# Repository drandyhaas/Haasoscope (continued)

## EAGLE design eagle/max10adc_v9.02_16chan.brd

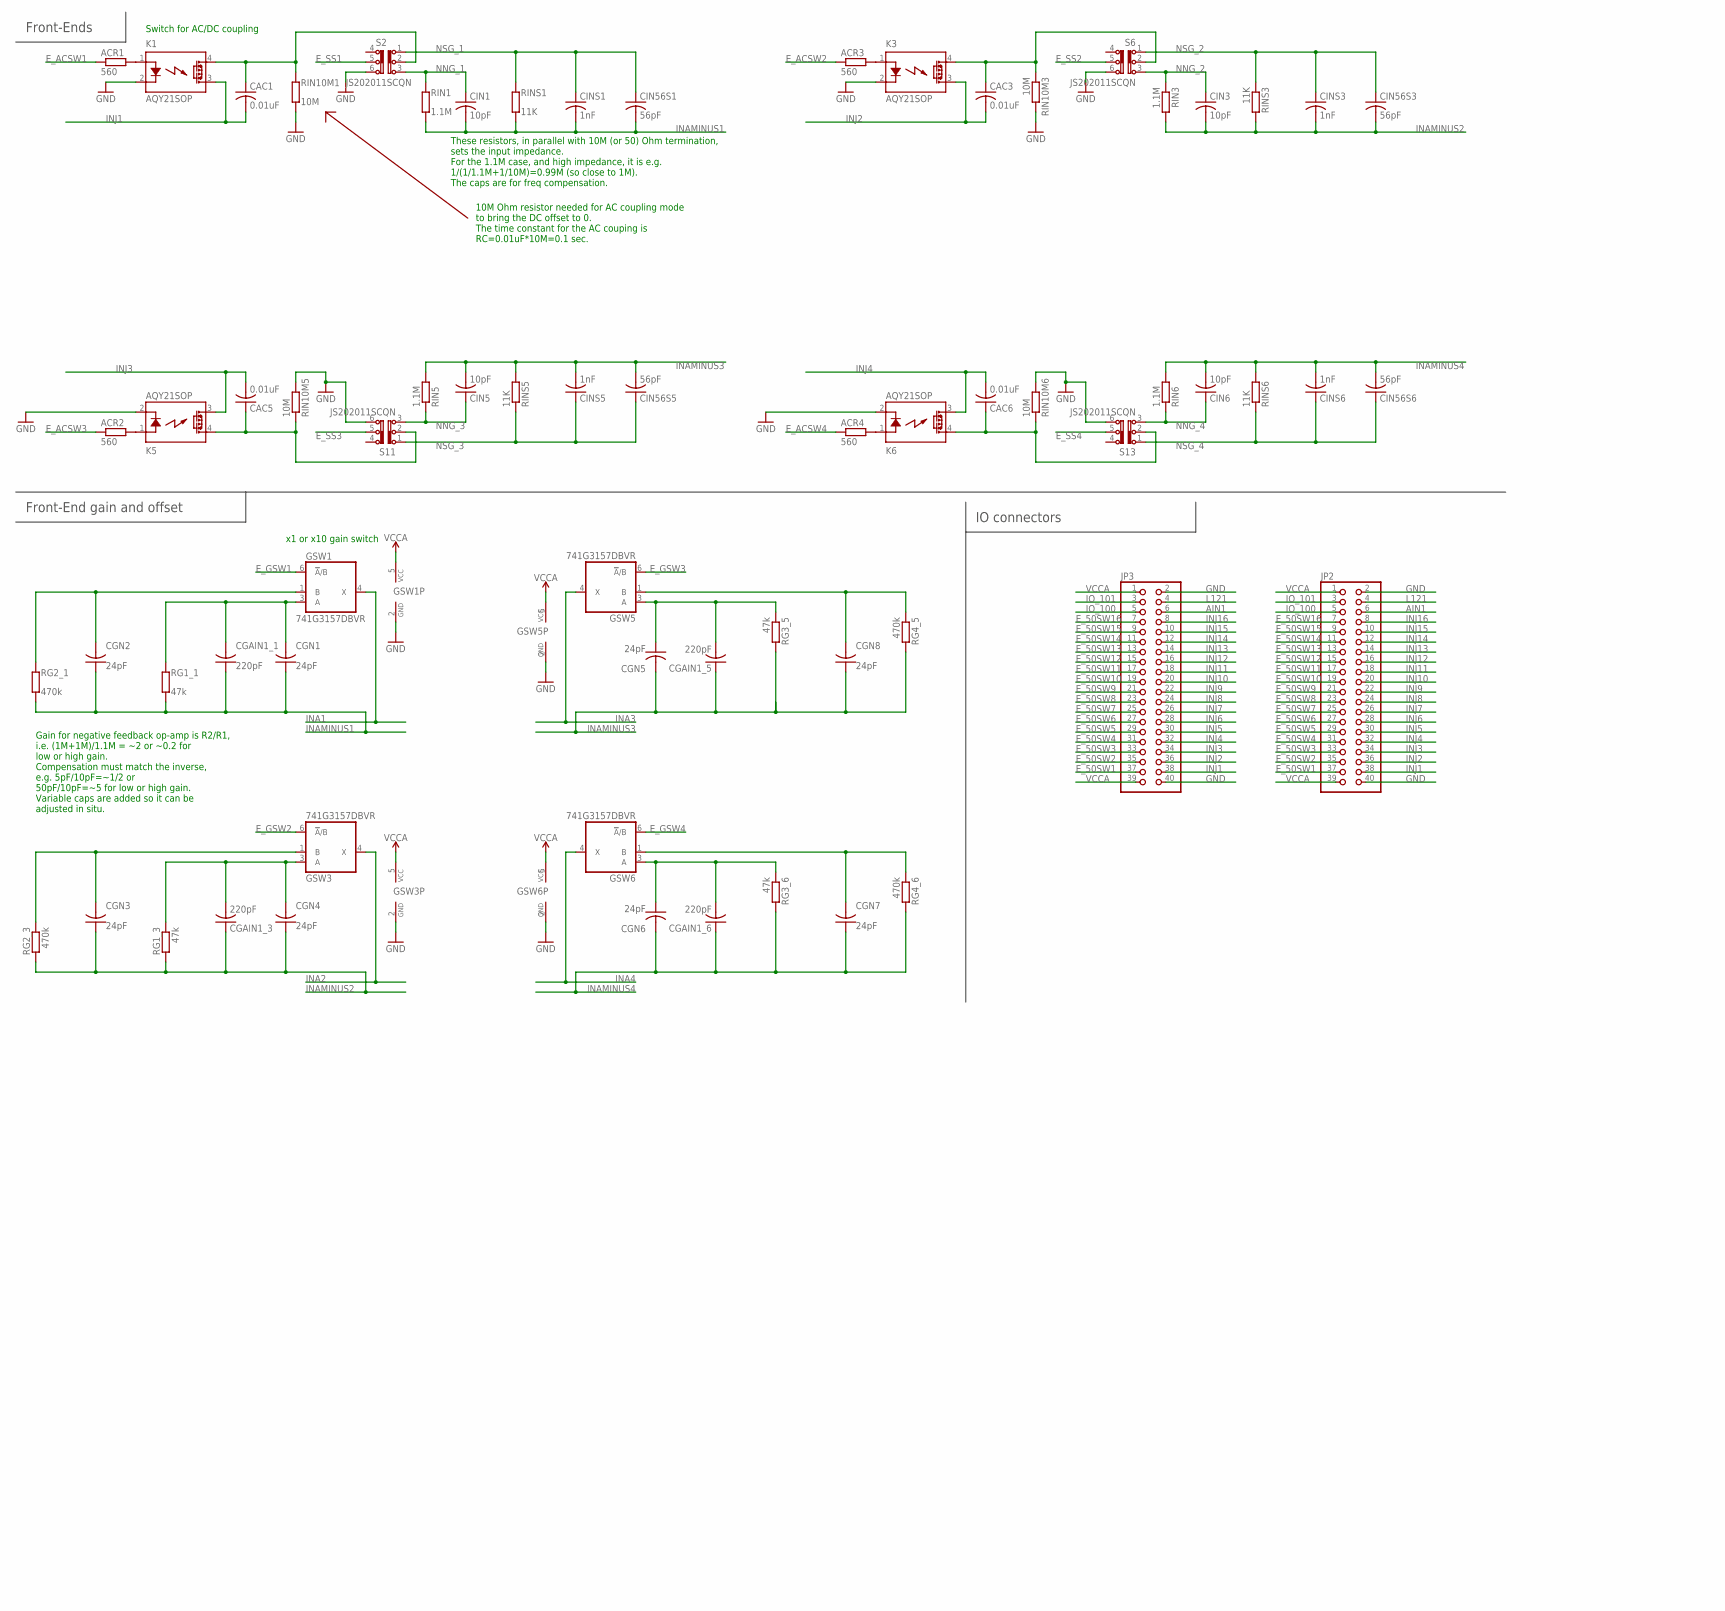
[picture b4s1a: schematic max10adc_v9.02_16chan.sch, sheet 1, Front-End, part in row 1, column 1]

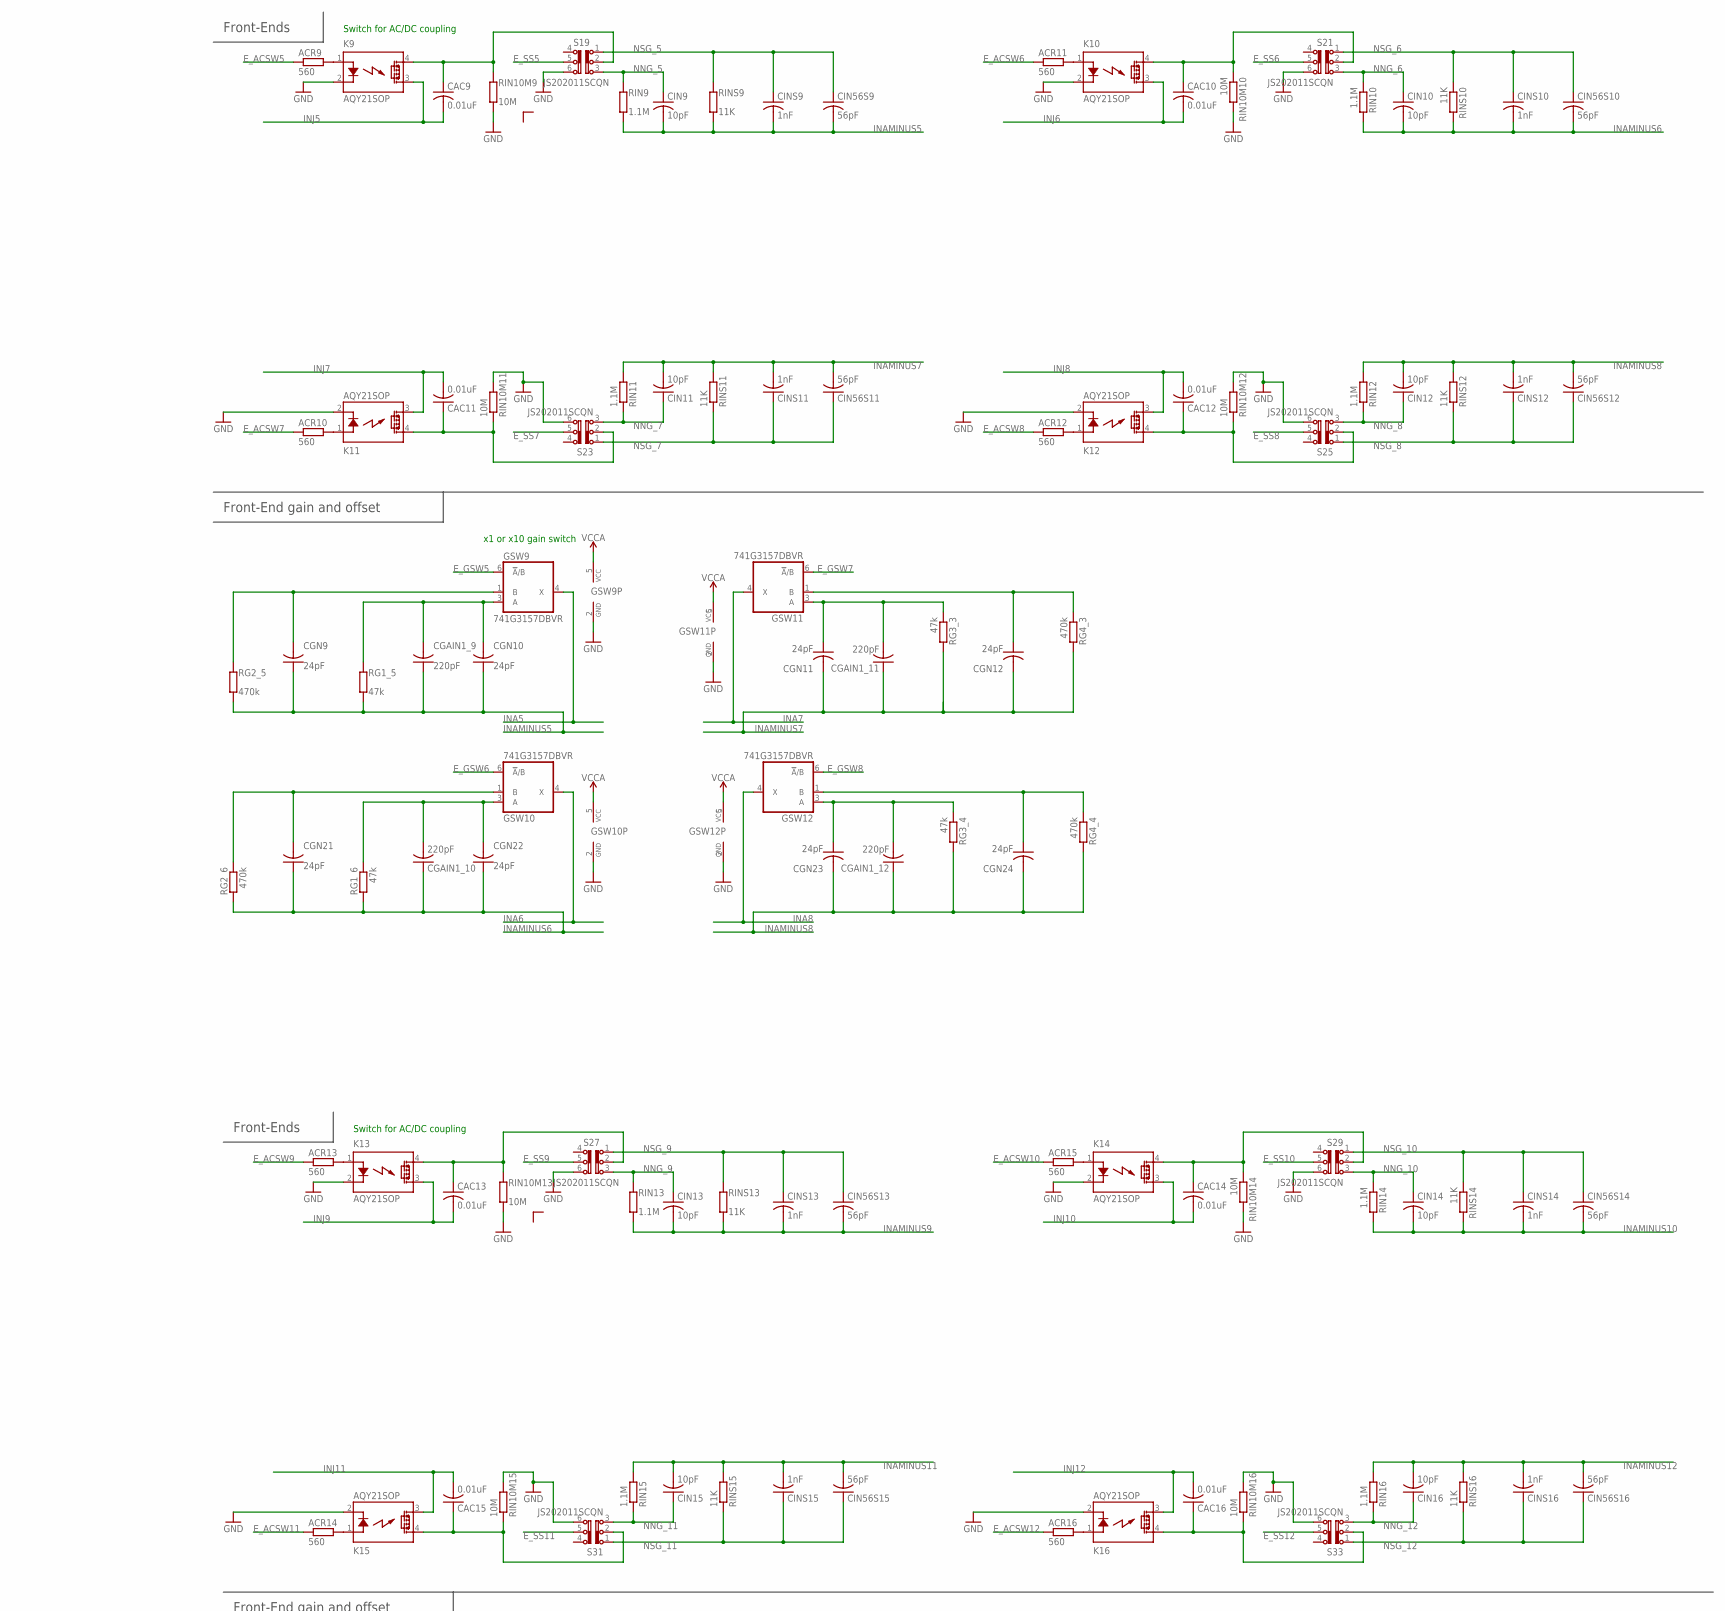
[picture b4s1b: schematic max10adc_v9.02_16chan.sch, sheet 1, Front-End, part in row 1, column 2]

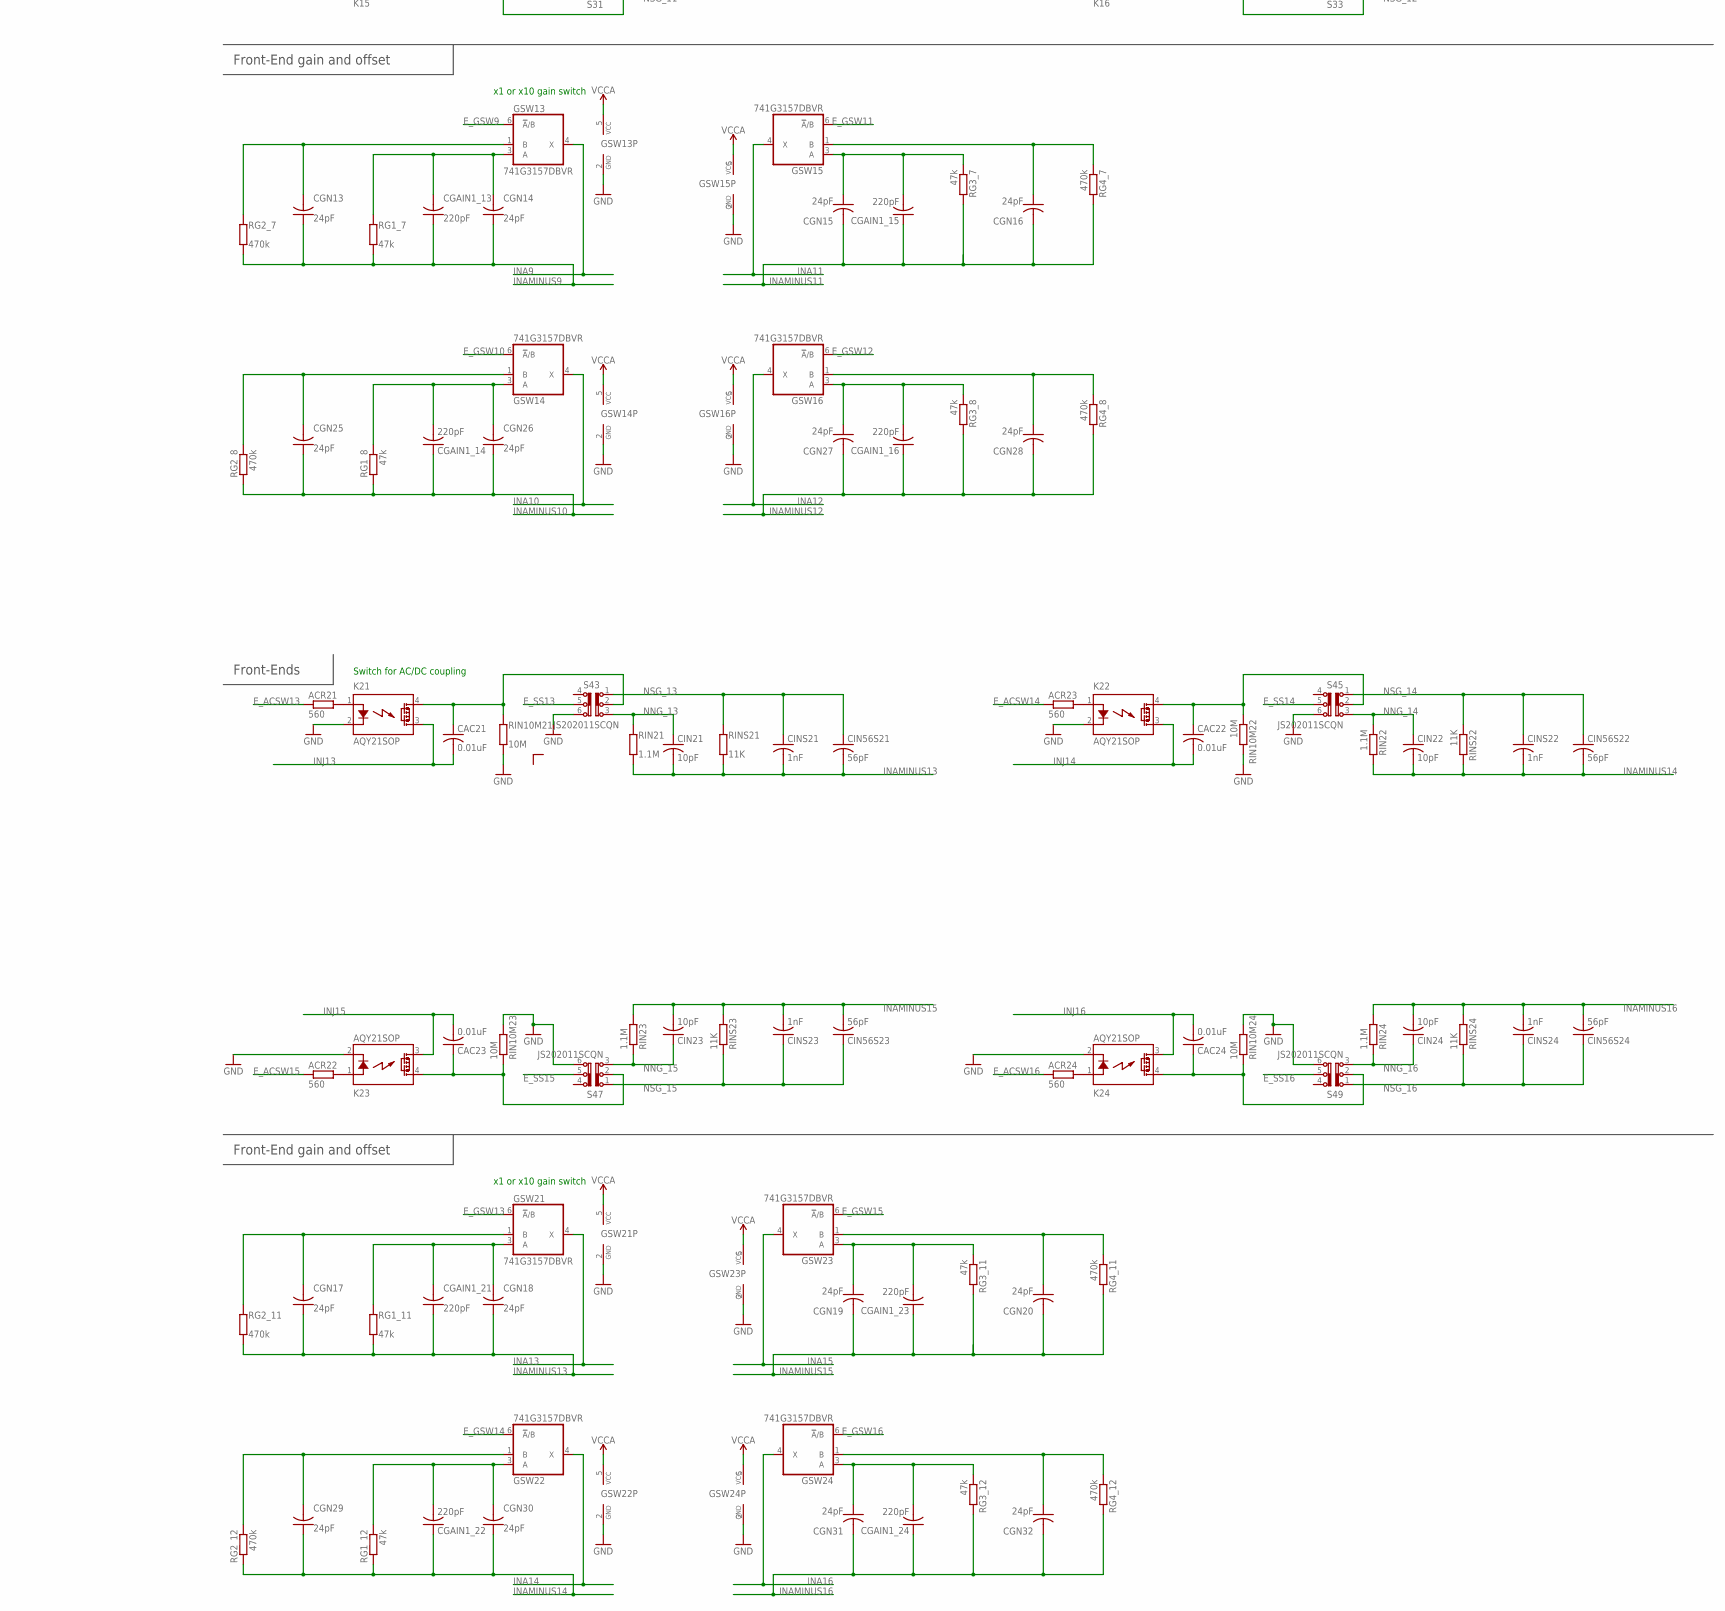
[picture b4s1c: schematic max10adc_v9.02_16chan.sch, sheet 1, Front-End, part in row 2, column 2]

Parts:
ACR1, ACR2, ACR3, ACR4, ACR9, ACR10, ACR11, ACR12, ACR13, ACR14, ACR15, ACR16, ACR21, ACR22, ACR23, ACR24: 560; R0805; MPN MF-RES-0805-560
CAC1, CAC3, CAC5, CAC6, CAC9, CAC10, CAC11, CAC12, CAC13, CAC14, CAC15, CAC16, CAC21, CAC22, CAC23, CAC24: 0.01uF; C0603
CGAIN1_1, CGAIN1_3, CGAIN1_5, CGAIN1_6, CGAIN1_9, CGAIN1_10, CGAIN1_11, CGAIN1_12, CGAIN1_13, CGAIN1_14, CGAIN1_15, CGAIN1_16, CGAIN1_21, CGAIN1_22, CGAIN1_23, CGAIN1_24: 220pF; C0603
CGN1, CGN2, CGN3, CGN4, CGN5, CGN6, CGN7, CGN8, CGN9, CGN10, CGN11, CGN12, CGN13, CGN14, CGN15, CGN16, CGN17, CGN18, CGN19, CGN20, CGN21, CGN22, CGN23, CGN24, CGN25, CGN26, CGN27, CGN28, CGN29, CGN30, CGN31, CGN32: 24pF; C0603
CIN1, CIN3, CIN5, CIN6, CIN9, CIN10, CIN11, CIN12, CIN13, CIN14, CIN15, CIN16, CIN21, CIN22, CIN23, CIN24: 10pF; C0603; MPN MF-CAP-0603-10pF
CIN56S1, CIN56S3, CIN56S5, CIN56S6, CIN56S9, CIN56S10, CIN56S11, CIN56S12, CIN56S13, CIN56S14, CIN56S15, CIN56S16, CIN56S21, CIN56S22, CIN56S23, CIN56S24: 56pF; C0603; MPN 06035A560FAT2A
CINS1, CINS3, CINS5, CINS6, CINS9, CINS10, CINS11, CINS12, CINS13, CINS14, CINS15, CINS16, CINS21, CINS22, CINS23, CINS24: 1nF; C0603; MPN 06035A102JAT2A
GSW1, GSW3, GSW5, GSW6, GSW9, GSW10, GSW11, GSW12, GSW13, GSW14, GSW15, GSW16, GSW21, GSW22, GSW23, GSW24: 741G3157DBVR; DBV_R-PDSO-G6; MPN SN74LVC1G3157DBV
JP2: PINHD-2X20/90; 2X20/90
JP3: PINHD-2X20; 2X20
K1, K3, K5, K6, K9, K10, K11, K12, K13, K14, K15, K16, K21, K22, K23, K24: AQY21SOP; SOP04; MPN AQY210S
RG1_1, RG1_3, RG1_5, RG1_6, RG1_7, RG1_8, RG1_11, RG1_12, RG3_3, RG3_4, RG3_5, RG3_6, RG3_7, RG3_8, RG3_11, RG3_12: 47k; R0805
RG2_1, RG2_3, RG2_5, RG2_6, RG2_7, RG2_8, RG2_11, RG2_12, RG4_3, RG4_4, RG4_5, RG4_6, RG4_7, RG4_8, RG4_11, RG4_12: 470k; R0805
RIN1, RIN3, RIN5, RIN6, RIN9, RIN10, RIN11, RIN12, RIN13, RIN14, RIN15, RIN16, RIN21, RIN22, RIN23, RIN24: 1.1M; R0805; MPN CRCW08051M10FKEA
RIN10M1, RIN10M3, RIN10M5, RIN10M6, RIN10M9, RIN10M10, RIN10M11, RIN10M12, RIN10M13, RIN10M14, RIN10M15, RIN10M16, RIN10M21, RIN10M22, RIN10M23, RIN10M24: 10M; R0805; MPN CRCW080510M0FKEB
RINS1, RINS3, RINS5, RINS6, RINS9, RINS10, RINS11, RINS12, RINS13, RINS14, RINS15, RINS16, RINS21, RINS22, RINS23, RINS24: 11K; R0805; MPN CRCW080511K0FKEA
S2, S6, S11, S13, S19, S21, S23, S25, S27, S29, S31, S33, S43, S45, S47, S49: JS202011SCQN

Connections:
AIN1: JP2.6, JP3.6; also elsewhere on the board
CGAIN1: CGAIN1_1.2, CGN1.2, GSW1.3 (A), RG1_1.1
CGAIN2: CGN2.2, GSW1.1 (B), RG2_1.1
CGAIN5: CGAIN1_3.2, CGN4.2, GSW3.3 (A), RG1_3.1
CGAIN6: CGN3.2, GSW3.1 (B), RG2_3.1
CGAIN9: CGAIN1_5.2, CGN5.1, GSW5.3 (A), RG3_5.1
CGAIN10: CGN8.2, GSW5.1 (B), RG4_5.1
CGAIN11: CGAIN1_6.2, CGN6.1, GSW6.3 (A), RG3_6.1
CGAIN12: CGN7.2, GSW6.1 (B), RG4_6.1
CGAIN17: CGAIN1_9.2, CGN10.2, GSW9.3 (A), RG1_5.1
CGAIN18: CGN9.2, GSW9.1 (B), RG2_5.1
CGAIN19: CGAIN1_10.2, CGN22.2, GSW10.3 (A), RG1_6.1
CGAIN20: CGN21.2, GSW10.1 (B), RG2_6.1
CGAIN21: CGAIN1_11.2, CGN11.1, GSW11.3 (A), RG3_3.1
CGAIN22: CGN12.1, GSW11.1 (B), RG4_3.1
CGAIN23: CGAIN1_12.2, CGN23.1, GSW12.3 (A), RG3_4.1
CGAIN24: CGN24.1, GSW12.1 (B), RG4_4.1
CGAIN25: CGAIN1_13.2, CGN14.2, GSW13.3 (A), RG1_7.1
CGAIN26: CGN13.2, GSW13.1 (B), RG2_7.1
CGAIN27: CGAIN1_14.2, CGN26.2, GSW14.3 (A), RG1_8.1
CGAIN28: CGN25.2, GSW14.1 (B), RG2_8.1
CGAIN29: CGAIN1_15.2, CGN15.1, GSW15.3 (A), RG3_7.1
CGAIN30: CGN16.1, GSW15.1 (B), RG4_7.1
CGAIN31: CGAIN1_16.2, CGN27.1, GSW16.3 (A), RG3_8.1
CGAIN32: CGN28.1, GSW16.1 (B), RG4_8.1
CGAIN41: CGAIN1_21.2, CGN18.2, GSW21.3 (A), RG1_11.1
CGAIN42: CGN17.2, GSW21.1 (B), RG2_11.1
CGAIN43: CGAIN1_22.2, CGN30.2, GSW22.3 (A), RG1_12.1
CGAIN44: CGN29.2, GSW22.1 (B), RG2_12.1
CGAIN45: CGAIN1_23.2, CGN19.1, GSW23.3 (A), RG3_11.1
CGAIN46: CGN20.1, GSW23.1 (B), RG4_11.1
CGAIN47: CGAIN1_24.2, CGN31.1, GSW24.3 (A), RG3_12.1
CGAIN48: CGN32.1, GSW24.1 (B), RG4_12.1
E_50SW1: JP2.37, JP3.37; also elsewhere on the board
E_50SW2: JP2.35, JP3.35; also elsewhere on the board
E_50SW3: JP2.33, JP3.33; also elsewhere on the board
E_50SW4: JP2.31, JP3.31; also elsewhere on the board
E_50SW5: JP2.29, JP3.29; also elsewhere on the board
E_50SW6: JP2.27, JP3.27; also elsewhere on the board
E_50SW7: JP2.25, JP3.25; also elsewhere on the board
E_50SW8: JP2.23, JP3.23; also elsewhere on the board
E_50SW9: JP2.21, JP3.21; also elsewhere on the board
E_50SW10: JP2.19, JP3.19; also elsewhere on the board
E_50SW11: JP2.17, JP3.17; also elsewhere on the board
E_50SW12: JP2.15, JP3.15; also elsewhere on the board
E_50SW13: JP2.13, JP3.13; also elsewhere on the board
E_50SW14: JP2.11, JP3.11; also elsewhere on the board
E_50SW15: JP2.9, JP3.9; also elsewhere on the board
E_50SW16: JP2.7, JP3.7; also elsewhere on the board
E_ACSW1: ACR1.1; also elsewhere on the board
E_ACSW2: ACR3.1; also elsewhere on the board
E_ACSW3: ACR2.1; also elsewhere on the board
E_ACSW4: ACR4.1; also elsewhere on the board
E_ACSW5: ACR9.1; also elsewhere on the board
E_ACSW6: ACR11.1; also elsewhere on the board
E_ACSW7: ACR10.1; also elsewhere on the board
E_ACSW8: ACR12.1; also elsewhere on the board
E_ACSW9: ACR13.1; also elsewhere on the board
E_ACSW10: ACR15.1; also elsewhere on the board
E_ACSW11: ACR14.1; also elsewhere on the board
E_ACSW12: ACR16.1; also elsewhere on the board
E_ACSW13: ACR21.1; also elsewhere on the board
E_ACSW14: ACR23.1; also elsewhere on the board
E_ACSW15: ACR22.1; also elsewhere on the board
E_ACSW16: ACR24.1; also elsewhere on the board
E_GSW1: GSW1.6 (!A!/B); also elsewhere on the board
E_GSW2: GSW3.6 (!A!/B); also elsewhere on the board
E_GSW3: GSW5.6 (!A!/B); also elsewhere on the board
E_GSW4: GSW6.6 (!A!/B); also elsewhere on the board
E_GSW5: GSW9.6 (!A!/B); also elsewhere on the board
E_GSW6: GSW10.6 (!A!/B); also elsewhere on the board
E_GSW7: GSW11.6 (!A!/B); also elsewhere on the board
E_GSW8: GSW12.6 (!A!/B); also elsewhere on the board
E_GSW9: GSW13.6 (!A!/B); also elsewhere on the board
E_GSW10: GSW14.6 (!A!/B); also elsewhere on the board
E_GSW11: GSW15.6 (!A!/B); also elsewhere on the board
E_GSW12: GSW16.6 (!A!/B); also elsewhere on the board
E_GSW13: GSW21.6 (!A!/B); also elsewhere on the board
E_GSW14: GSW22.6 (!A!/B); also elsewhere on the board
E_GSW15: GSW23.6 (!A!/B); also elsewhere on the board
E_GSW16: GSW24.6 (!A!/B); also elsewhere on the board
E_SS1: S2.5; also elsewhere on the board
E_SS2: S6.5; also elsewhere on the board
E_SS3: S11.5; also elsewhere on the board
E_SS4: S13.5; also elsewhere on the board
E_SS5: S19.5; also elsewhere on the board
E_SS6: S21.5; also elsewhere on the board
E_SS7: S23.5; also elsewhere on the board
E_SS8: S25.5; also elsewhere on the board
E_SS9: S27.5; also elsewhere on the board
E_SS10: S29.5; also elsewhere on the board
E_SS11: S31.5; also elsewhere on the board
E_SS12: S33.5; also elsewhere on the board
E_SS13: S43.5; also elsewhere on the board
E_SS14: S45.5; also elsewhere on the board
E_SS15: S47.5; also elsewhere on the board
E_SS16: S49.5; also elsewhere on the board
GND: GSW1.2 (GND), GSW3.2 (GND), GSW5.2 (GND), GSW6.2 (GND), GSW9.2 (GND), GSW10.2 (GND), GSW11.2 (GND), GSW12.2 (GND), GSW13.2 (GND), GSW14.2 (GND), GSW15.2 (GND), GSW16.2 (GND), GSW21.2 (GND), GSW22.2 (GND), GSW23.2 (GND), GSW24.2 (GND), JP2.2, JP2.40, JP3.2, JP3.40, K1.2 (K), K3.2 (K), K5.2 (K), K6.2 (K), K9.2 (K), K10.2 (K), K11.2 (K), K12.2 (K), K13.2 (K), K14.2 (K), K15.2 (K), K16.2 (K), K21.2 (K), K22.2 (K), K23.2 (K), K24.2 (K), RIN10M1.2, RIN10M3.2, RIN10M5.2, RIN10M6.2, RIN10M9.2, RIN10M10.2, RIN10M11.2, RIN10M12.2, RIN10M13.2, RIN10M14.2, RIN10M15.2, RIN10M16.2, RIN10M21.2, RIN10M22.2, RIN10M23.2, RIN10M24.2, S2.6, S6.6, S11.6, S13.6, S19.6, S21.6, S23.6, S25.6, S27.6, S29.6, S31.6, S33.6, S43.6, S45.6, S47.6, S49.6; also elsewhere on the board
INA1: GSW1.4 (X); also elsewhere on the board
INA2: GSW3.4 (X); also elsewhere on the board
INA3: GSW5.4 (X); also elsewhere on the board
INA4: GSW6.4 (X); also elsewhere on the board
INA5: GSW9.4 (X); also elsewhere on the board
INA6: GSW10.4 (X); also elsewhere on the board
INA7: GSW11.4 (X); also elsewhere on the board
INA8: GSW12.4 (X); also elsewhere on the board
INA9: GSW13.4 (X); also elsewhere on the board
INA10: GSW14.4 (X); also elsewhere on the board
INA11: GSW15.4 (X); also elsewhere on the board
INA12: GSW16.4 (X); also elsewhere on the board
INA13: GSW21.4 (X); also elsewhere on the board
INA14: GSW22.4 (X); also elsewhere on the board
INA15: GSW23.4 (X); also elsewhere on the board
INA16: GSW24.4 (X); also elsewhere on the board
INAMINUS1: CGAIN1_1.1, CGN1.1, CGN2.1, CIN1.2, CIN56S1.2, CINS1.2, RG1_1.2, RG2_1.2, RIN1.2, RINS1.2; also elsewhere on the board
INAMINUS2: CGAIN1_3.1, CGN3.1, CGN4.1, CIN3.2, CIN56S3.2, CINS3.2, RG1_3.2, RG2_3.2, RIN3.2, RINS3.2; also elsewhere on the board
INAMINUS3: CGAIN1_5.1, CGN5.2, CGN8.1, CIN5.2, CIN56S5.2, CINS5.2, RG3_5.2, RG4_5.2, RIN5.2, RINS5.2; also elsewhere on the board
INAMINUS4: CGAIN1_6.1, CGN6.2, CGN7.1, CIN6.2, CIN56S6.2, CINS6.2, RG3_6.2, RG4_6.2, RIN6.2, RINS6.2; also elsewhere on the board
INAMINUS5: CGAIN1_9.1, CGN9.1, CGN10.1, CIN9.2, CIN56S9.2, CINS9.2, RG1_5.2, RG2_5.2, RIN9.2, RINS9.2; also elsewhere on the board
INAMINUS6: CGAIN1_10.1, CGN21.1, CGN22.1, CIN10.2, CIN56S10.2, CINS10.2, RG1_6.2, RG2_6.2, RIN10.2, RINS10.2; also elsewhere on the board
INAMINUS7: CGAIN1_11.1, CGN11.2, CGN12.2, CIN11.2, CIN56S11.2, CINS11.2, RG3_3.2, RG4_3.2, RIN11.2, RINS11.2; also elsewhere on the board
INAMINUS8: CGAIN1_12.1, CGN23.2, CGN24.2, CIN12.2, CIN56S12.2, CINS12.2, RG3_4.2, RG4_4.2, RIN12.2, RINS12.2; also elsewhere on the board
INAMINUS9: CGAIN1_13.1, CGN13.1, CGN14.1, CIN13.2, CIN56S13.2, CINS13.2, RG1_7.2, RG2_7.2, RIN13.2, RINS13.2; also elsewhere on the board
INAMINUS10: CGAIN1_14.1, CGN25.1, CGN26.1, CIN14.2, CIN56S14.2, CINS14.2, RG1_8.2, RG2_8.2, RIN14.2, RINS14.2; also elsewhere on the board
INAMINUS11: CGAIN1_15.1, CGN15.2, CGN16.2, CIN15.2, CIN56S15.2, CINS15.2, RG3_7.2, RG4_7.2, RIN15.2, RINS15.2; also elsewhere on the board
INAMINUS12: CGAIN1_16.1, CGN27.2, CGN28.2, CIN16.2, CIN56S16.2, CINS16.2, RG3_8.2, RG4_8.2, RIN16.2, RINS16.2; also elsewhere on the board
INAMINUS13: CGAIN1_21.1, CGN17.1, CGN18.1, CIN21.2, CIN56S21.2, CINS21.2, RG1_11.2, RG2_11.2, RIN21.2, RINS21.2; also elsewhere on the board
INAMINUS14: CGAIN1_22.1, CGN29.1, CGN30.1, CIN22.2, CIN56S22.2, CINS22.2, RG1_12.2, RG2_12.2, RIN22.2, RINS22.2; also elsewhere on the board
INAMINUS15: CGAIN1_23.1, CGN19.2, CGN20.2, CIN23.2, CIN56S23.2, CINS23.2, RG3_11.2, RG4_11.2, RIN23.2, RINS23.2; also elsewhere on the board
INAMINUS16: CGAIN1_24.1, CGN31.2, CGN32.2, CIN24.2, CIN56S24.2, CINS24.2, RG3_12.2, RG4_12.2, RIN24.2, RINS24.2; also elsewhere on the board
INJ1: CAC1.2, JP2.38, JP3.38, K1.3 (DS2)
INJ2: CAC3.2, JP2.36, JP3.36, K3.3 (DS2)
INJ3: CAC5.2, JP2.34, JP3.34, K5.3 (DS2)
INJ4: CAC6.2, JP2.32, JP3.32, K6.3 (DS2)
INJ5: CAC9.2, JP2.30, JP3.30, K9.3 (DS2)
INJ6: CAC10.2, JP2.28, JP3.28, K10.3 (DS2)
INJ7: CAC11.2, JP2.26, JP3.26, K11.3 (DS2)
INJ8: CAC12.2, JP2.24, JP3.24, K12.3 (DS2)
INJ9: CAC13.2, JP2.22, JP3.22, K13.3 (DS2)
INJ10: CAC14.2, JP2.20, JP3.20, K14.3 (DS2)
INJ11: CAC15.2, JP2.18, JP3.18, K15.3 (DS2)
INJ12: CAC16.2, JP2.16, JP3.16, K16.3 (DS2)
INJ13: CAC21.2, JP2.14, JP3.14, K21.3 (DS2)
INJ14: CAC22.2, JP2.12, JP3.12, K22.3 (DS2)
INJ15: CAC23.2, JP2.10, JP3.10, K23.3 (DS2)
INJ16: CAC24.2, JP2.8, JP3.8, K24.3 (DS2)
IO_100: JP2.5, JP3.5; also elsewhere on the board
IO_101: JP2.3, JP3.3; also elsewhere on the board
L121: JP2.4, JP3.4; also elsewhere on the board
unnamed: ACR11.2, K10.1 (A)
unnamed: ACR10.2, K11.1 (A)
unnamed: ACR2.2, K5.1 (A)
unnamed: ACR3.2, K3.1 (A)
unnamed: ACR4.2, K6.1 (A)
unnamed: ACR12.2, K12.1 (A)
unnamed: ACR13.2, K13.1 (A)
unnamed: CAC3.1, K3.4 (DS1), RIN10M3.1, S6.2
unnamed: CAC1.1, K1.4 (DS1), RIN10M1.1, S2.2
unnamed: ACR1.2, K1.1 (A)
unnamed: CAC5.1, K5.4 (DS1), RIN10M5.1, S11.2
unnamed: CAC6.1, K6.4 (DS1), RIN10M6.1, S13.2
unnamed: CAC9.1, K9.4 (DS1), RIN10M9.1, S19.2
unnamed: CAC10.1, K10.4 (DS1), RIN10M10.1, S21.2
unnamed: CAC11.1, K11.4 (DS1), RIN10M11.1, S23.2
unnamed: CAC12.1, K12.4 (DS1), RIN10M12.1, S25.2
unnamed: ACR15.2, K14.1 (A)
unnamed: ACR14.2, K15.1 (A)
unnamed: ACR16.2, K16.1 (A)
unnamed: ACR21.2, K21.1 (A)
unnamed: CAC13.1, K13.4 (DS1), RIN10M13.1, S27.2
unnamed: CAC14.1, K14.4 (DS1), RIN10M14.1, S29.2
unnamed: CAC15.1, K15.4 (DS1), RIN10M15.1, S31.2
unnamed: CAC16.1, K16.4 (DS1), RIN10M16.1, S33.2
unnamed: ACR23.2, K22.1 (A)
unnamed: ACR22.2, K23.1 (A)
unnamed: ACR24.2, K24.1 (A)
unnamed: ACR9.2, K9.1 (A)
unnamed: CAC21.1, K21.4 (DS1), RIN10M21.1, S43.2
unnamed: CAC22.1, K22.4 (DS1), RIN10M22.1, S45.2
unnamed: CAC23.1, K23.4 (DS1), RIN10M23.1, S47.2
unnamed: CAC24.1, K24.4 (DS1), RIN10M24.1, S49.2
NNG_1: CIN1.1, RIN1.1, S2.3
NNG_2: CIN3.1, RIN3.1, S6.3
NNG_3: CIN5.1, RIN5.1, S11.3
NNG_4: CIN6.1, RIN6.1, S13.3
NNG_5: CIN9.1, RIN9.1, S19.3
NNG_6: CIN10.1, RIN10.1, S21.3
NNG_7: CIN11.1, RIN11.1, S23.3
NNG_8: CIN12.1, RIN12.1, S25.3
NNG_9: CIN13.1, RIN13.1, S27.3
NNG_10: CIN14.1, RIN14.1, S29.3
NNG_11: CIN15.1, RIN15.1, S31.3
NNG_12: CIN16.1, RIN16.1, S33.3
NNG_13: CIN21.1, RIN21.1, S43.3
NNG_14: CIN22.1, RIN22.1, S45.3
NNG_15: CIN23.1, RIN23.1, S47.3
NNG_16: CIN24.1, RIN24.1, S49.3
NSG_1: CIN56S1.1, CINS1.1, RINS1.1, S2.1
NSG_2: CIN56S3.1, CINS3.1, RINS3.1, S6.1
NSG_3: CIN56S5.1, CINS5.1, RINS5.1, S11.1
NSG_4: CIN56S6.1, CINS6.1, RINS6.1, S13.1
NSG_5: CIN56S9.1, CINS9.1, RINS9.1, S19.1
NSG_6: CIN56S10.1, CINS10.1, RINS10.1, S21.1
NSG_7: CIN56S11.1, CINS11.1, RINS11.1, S23.1
NSG_8: CIN56S12.1, CINS12.1, RINS12.1, S25.1
NSG_9: CIN56S13.1, CINS13.1, RINS13.1, S27.1
NSG_10: CIN56S14.1, CINS14.1, RINS14.1, S29.1
NSG_11: CIN56S15.1, CINS15.1, RINS15.1, S31.1
NSG_12: CIN56S16.1, CINS16.1, RINS16.1, S33.1
NSG_13: CIN56S21.1, CINS21.1, RINS21.1, S43.1
NSG_14: CIN56S22.1, CINS22.1, RINS22.1, S45.1
NSG_15: CIN56S23.1, CINS23.1, RINS23.1, S47.1
NSG_16: CIN56S24.1, CINS24.1, RINS24.1, S49.1
VCCA: GSW1.5 (VCC), GSW3.5 (VCC), GSW5.5 (VCC), GSW6.5 (VCC), GSW9.5 (VCC), GSW10.5 (VCC), GSW11.5 (VCC), GSW12.5 (VCC), GSW13.5 (VCC), GSW14.5 (VCC), GSW15.5 (VCC), GSW16.5 (VCC), GSW21.5 (VCC), GSW22.5 (VCC), GSW23.5 (VCC), GSW24.5 (VCC), JP2.1, JP2.39, JP3.1, JP3.39; also elsewhere on the board

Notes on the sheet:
Front-Ends
Front-End gain and offset
10M Ohm resistor needed for AC coupling mode to bring the DC offset to 0. The time constant for the AC couping is RC=0.01uF*10M=0.1 sec.
These resistors, in parallel with 10M (or 50) Ohm termination, sets the input impedance. For the 1.1M case, and high impedance, it is e.g. 1/(1/1.1M+1/10M)=0.99M (so close to 1M). The caps are for freq compensation.
Switch for AC/DC coupling
x1 or x10 gain switch
Gain for negative feedback op-amp is R2/R1, i.e. (1M+1M)/1.1M = ~2 or ~0.2 for low or high gain. Compensation must match the inverse, e.g. 5pF/10pF=~1/2 or 50pF/10pF=~5 for low or high gain. Variable caps are added so it can be adjusted in situ.
IO connectors
